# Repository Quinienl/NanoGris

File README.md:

# NanoGrids
### Arduino Nano version of Mutable Instruments Grids

Made this version  with Thru Hole parts and a Arduino Nano.
Schematics are heavely based on Mutable Instruments schematics. This is not a Mutable Instuments product.

_Note: panel hole for button might be a bit to big or small (depends if you use buttoncaps)_

I made this for my own and would like to share it with you. I'm doing this as a hobby so expect support to be like that to ;)
Everything at your own risk..

Some info on my website that might help

https://www.quinie.nl/category/diy/nanogris/

https://www.quinie.nl/nanogris-gallery/

If you don not want to order boards yourself please check out my shop.
https://www.quinie.nl/shop/

hex file for uploading here
https://www.quinie.nl/nanogris-the-hex-file/

Update: 6-8-2021
I updated the name of the module. The current version is 0.041

Older boards will have the same function. Did add some better ground planes. Some silkscreen additions to make build easier and changed the footprint of the potentiometer for better fit.

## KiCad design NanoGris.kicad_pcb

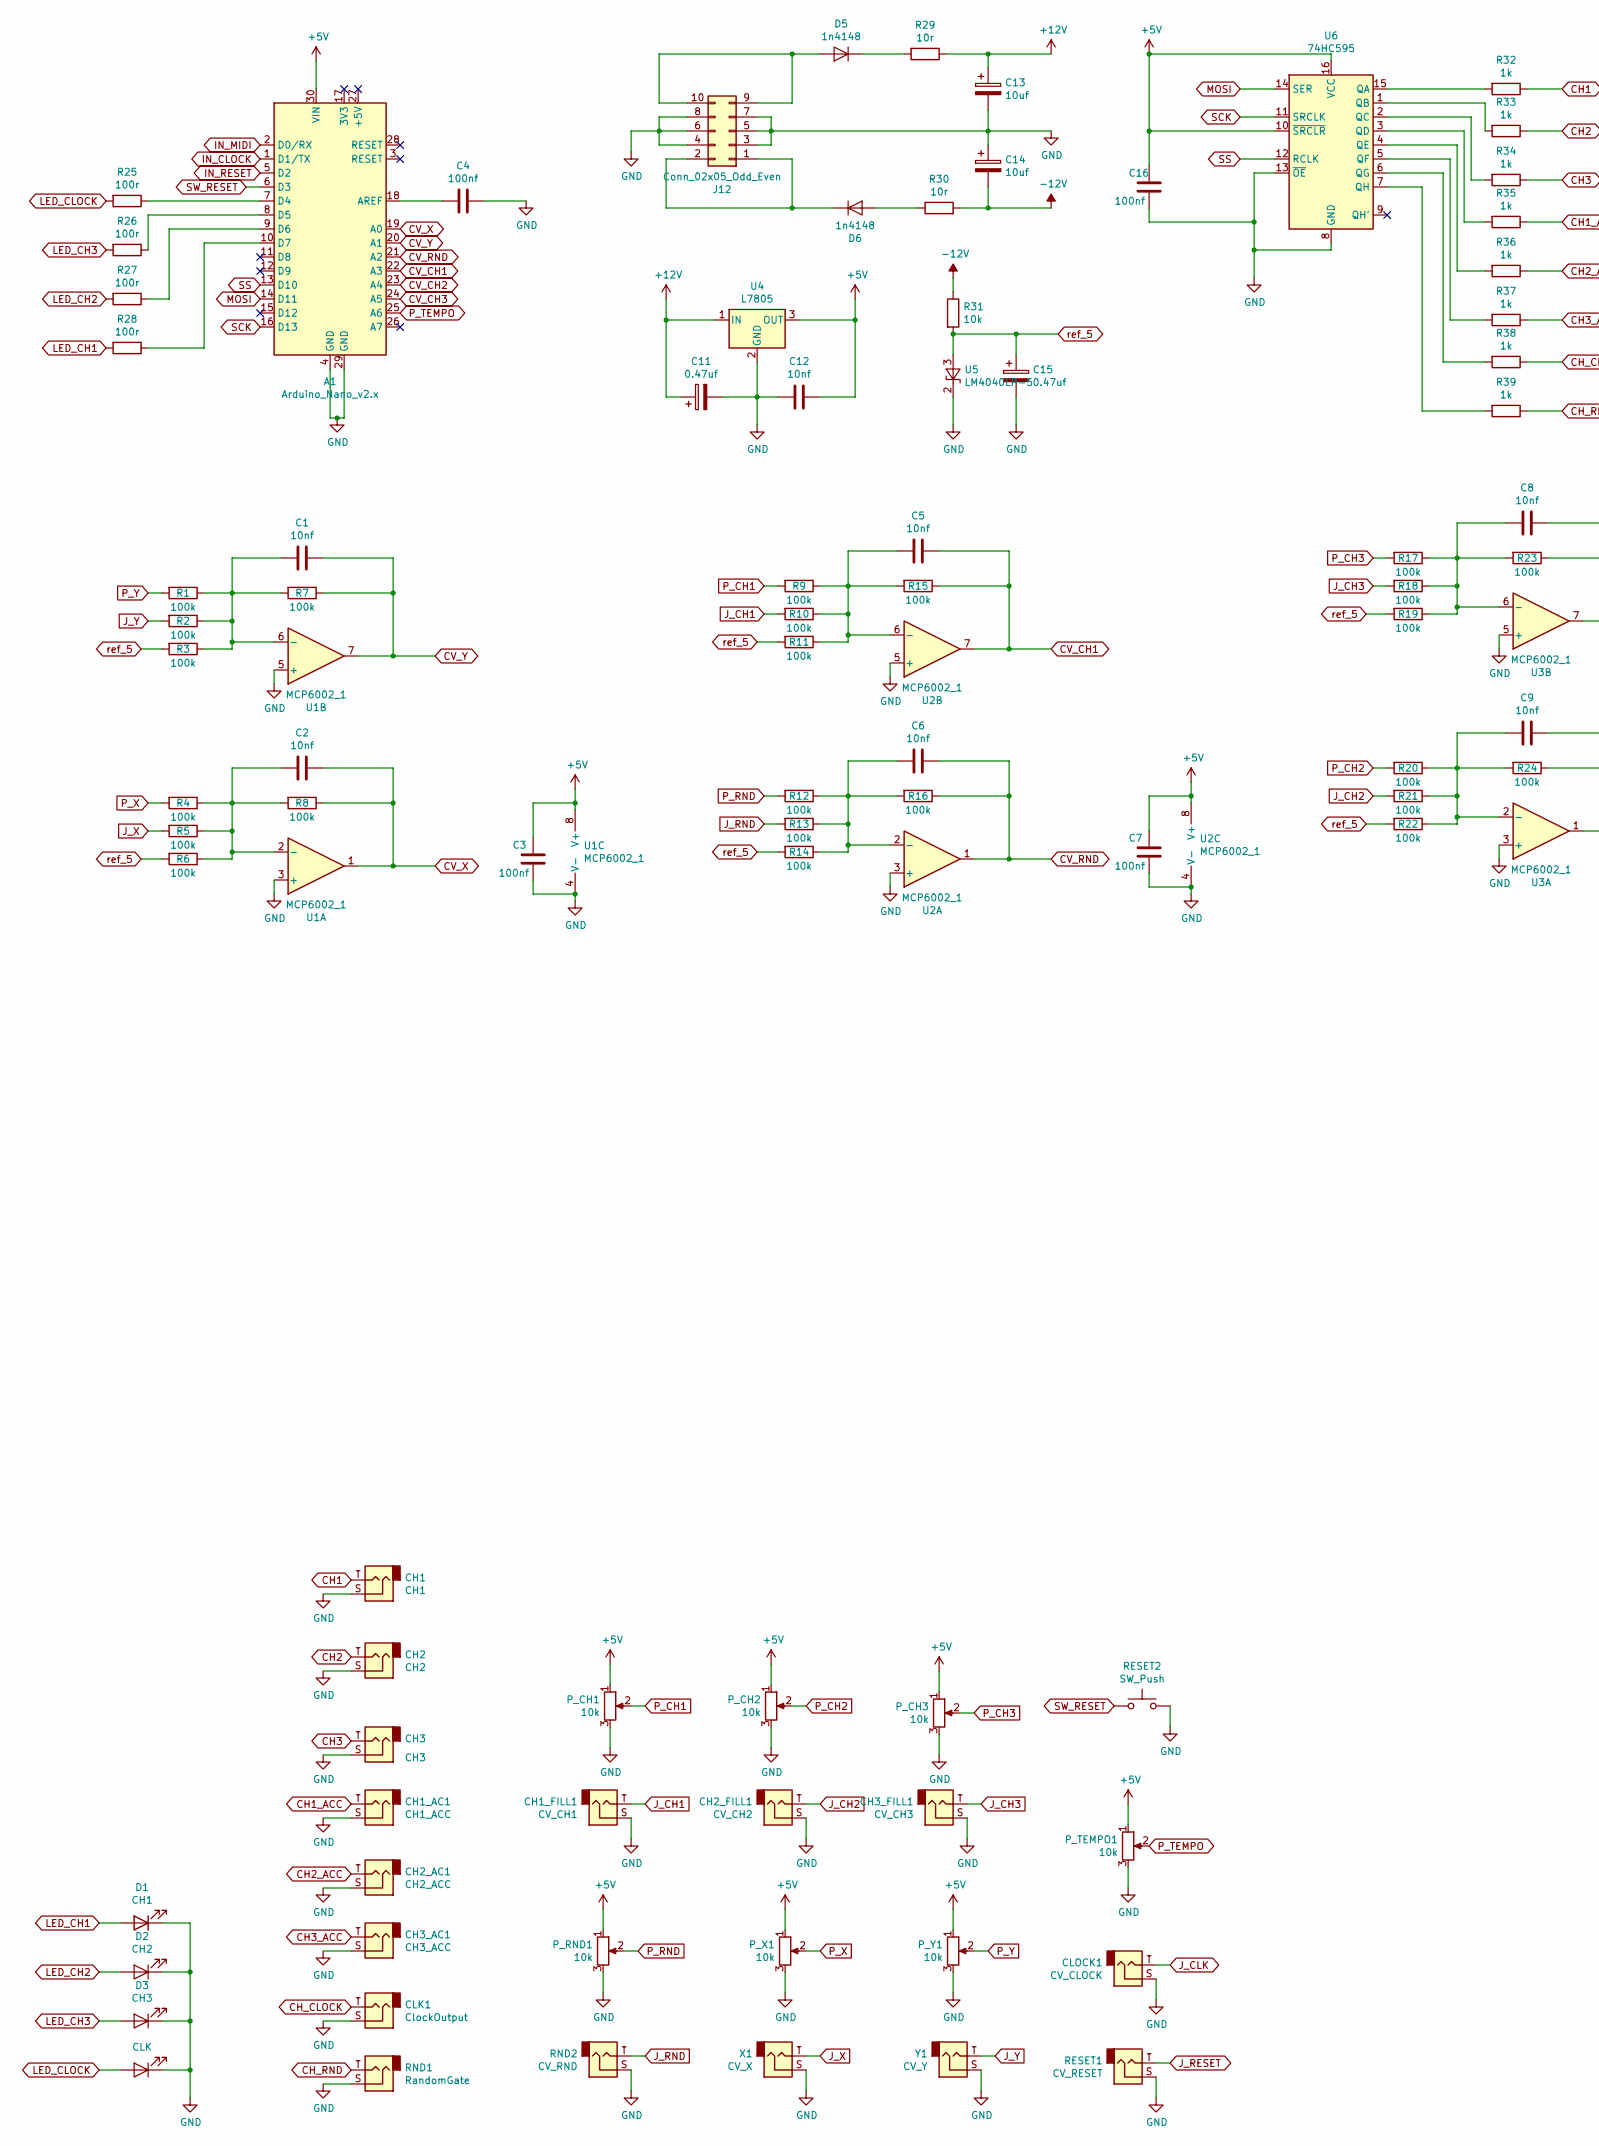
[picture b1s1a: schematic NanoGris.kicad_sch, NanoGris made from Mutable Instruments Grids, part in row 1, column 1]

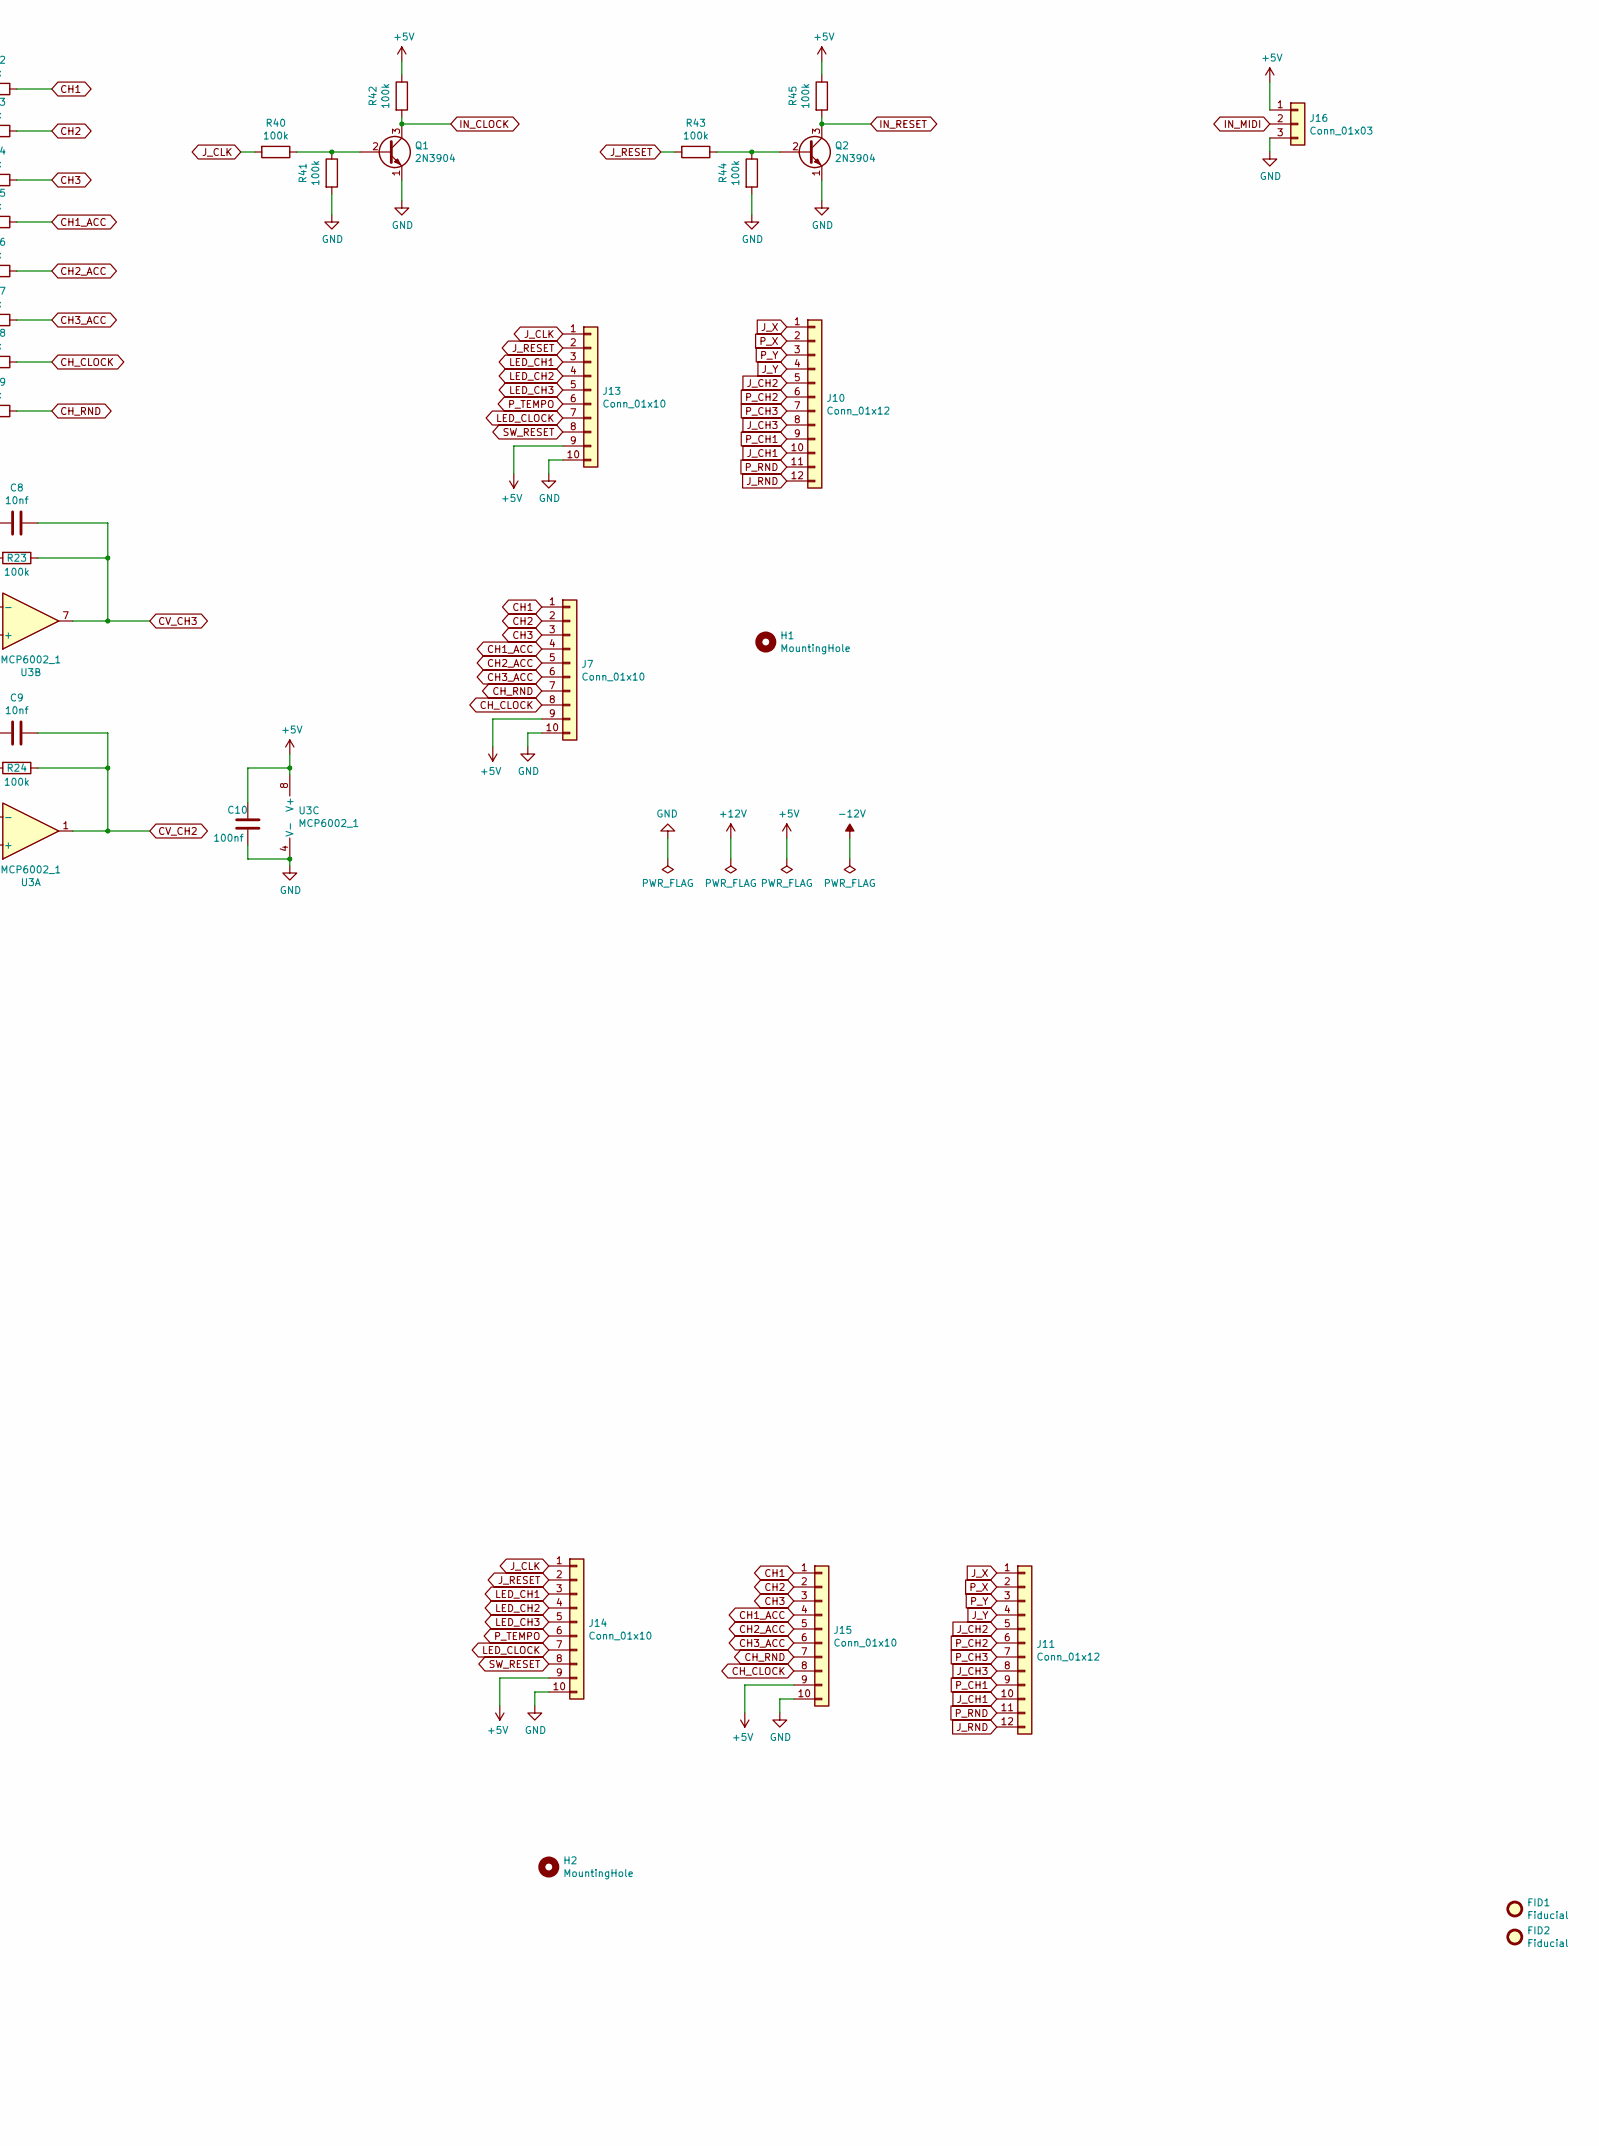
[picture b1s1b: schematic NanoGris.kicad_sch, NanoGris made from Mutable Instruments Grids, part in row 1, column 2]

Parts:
A1: Arduino_Nano_v2.x; Arduino_Nano
C1, C2, C5, C6, C8, C9, C12: 10nf; C_Disc_D5.0mm_W2.5mm_P2.50mm
C3, C4, C7, C10, C16: 100nf; C_Disc_D5.0mm_W2.5mm_P2.50mm
C11, C15: 0.47uf; CP_Radial_D5.0mm_P2.50mm
C13, C14: 10uf; CP_Radial_D5.0mm_P2.50mm
CH1: CH1; Jack_3.5mm_QingPu_WQP-PJ398SM_Vertical_CircularHoles
CH1_AC1: CH1_ACC; Jack_3.5mm_QingPu_WQP-PJ398SM_Vertical_CircularHoles
CH1_FILL1: CV_CH1; Jack_3.5mm_QingPu_WQP-PJ398SM_Vertical_CircularHoles
CH2: CH2; Jack_3.5mm_QingPu_WQP-PJ398SM_Vertical_CircularHoles
CH2_AC1: CH2_ACC; Jack_3.5mm_QingPu_WQP-PJ398SM_Vertical_CircularHoles
CH2_FILL1: CV_CH2; Jack_3.5mm_QingPu_WQP-PJ398SM_Vertical_CircularHoles
CH3: CH3; Jack_3.5mm_QingPu_WQP-PJ398SM_Vertical_CircularHoles
CH3_AC1: CH3_ACC; Jack_3.5mm_QingPu_WQP-PJ398SM_Vertical_CircularHoles
CH3_FILL1: CV_CH3; Jack_3.5mm_QingPu_WQP-PJ398SM_Vertical_CircularHoles
CLK1: ClockOutput; Jack_3.5mm_QingPu_WQP-PJ398SM_Vertical_CircularHoles
CLOCK1: CV_CLOCK; Jack_3.5mm_QingPu_WQP-PJ398SM_Vertical_CircularHoles
D1: CH1; LED_D3.0mm
D2: CH2; LED_D3.0mm
D3: CH3; LED_D3.0mm
D4: CLK; LED_D3.0mm
D5, D6: 1n4148; D_DO-34_SOD68_P7.62mm_Horizontal
FID1: Fiducial; OSHW-Logo2_7.3x6mm_SilkScreen
FID2: Fiducial; OSHW-Logo2_14.6x12mm_SilkScreen
H1, H2: MountingHole; MountingHole_3.2mm_M3
J7, J13: Conn_01x10; PinSocket_1x10_P2.54mm_Vertical
J10: Conn_01x12; PinSocket_1x12_P2.54mm_Vertical
J11: Conn_01x12; PinHeader_1x12_P2.54mm_Vertical
J12: Conn_02x05_Odd_Even; IDC-Header_2x05_P2.54mm_Vertical
J14, J15: Conn_01x10; PinHeader_1x10_P2.54mm_Vertical
J16: Conn_01x03; PinHeader_1x03_P2.54mm_Vertical
P_CH1, P_CH2, P_CH3: 10k; Potentiometer_Alps_RK09K_Single_Vertical_round
P_RND1: 10k; Potentiometer_Alps_RK09K_Single_Vertical_round
P_TEMPO1: 10k; Potentiometer_Alps_RK09K_Single_Vertical_round
P_X1: 10k; Potentiometer_Alps_RK09K_Single_Vertical_round
P_Y1: 10k; Potentiometer_Alps_RK09K_Single_Vertical_round
Q1, Q2: 2N3904; TO-92_Wide
R1, R2, R3, R4, R5, R6, R7, R8, R9, R10, R11, R12, R13, R14, R15, R16, R17, R18, R19, R20, R21, R22, R23, R24, R40, R41, R42, R43, R44, R45: 100k; R_Axial_DIN0204_L3.6mm_D1.6mm_P7.62mm_Horizontal
R25, R26, R27, R28: 100r; R_Axial_DIN0207_L6.3mm_D2.5mm_P7.62mm_Horizontal
R29, R30: 10r; R_Axial_DIN0204_L3.6mm_D1.6mm_P7.62mm_Horizontal
R31: 10k; R_Axial_DIN0204_L3.6mm_D1.6mm_P7.62mm_Horizontal
R32, R33, R34, R35, R36, R37, R38, R39: 1k; R_Axial_DIN0204_L3.6mm_D1.6mm_P7.62mm_Horizontal
RESET1: CV_RESET; Jack_3.5mm_QingPu_WQP-PJ398SM_Vertical_CircularHoles
RESET2: SW_Push; SW_PUSH_6mm
RND1: RandomGate; Jack_3.5mm_QingPu_WQP-PJ398SM_Vertical_CircularHoles
RND2: CV_RND; Jack_3.5mm_QingPu_WQP-PJ398SM_Vertical_CircularHoles
U1, U2, U3: MCP6002_1; DIP-8_W7.62mm
U4: L7805; TO-220-3_Vertical
U5: LM4040LP-5; TO-92_Wide
U6: 74HC595; DIP-16_W7.62mm
X1: CV_X; Jack_3.5mm_QingPu_WQP-PJ398SM_Vertical_CircularHoles
Y1: CV_Y; Jack_3.5mm_QingPu_WQP-PJ398SM_Vertical_CircularHoles

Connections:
+5V: A1.30 (VIN), C3.1, C7.1, C10.1, C12.1, C16.1, J7.9, J13.9, J14.9, J15.9, J16.1, P_CH1.1, P_CH2.1, P_CH3.1, P_RND1.1, P_TEMPO1.1, P_X1.1, P_Y1.1, R42.1, R45.1, U1.8 (V+), U2.8 (V+), U3.8 (V+), U4.3 (OUT), U6.10 (~SRCLR), U6.16 (VCC)
+12V: C11.1, C13.1, R29.1, U4.1 (IN)
-12V: C14.2, R30.2, R31.1
CH1: CH1.T, J7.1, J15.1, R32.1
CH1_ACC: CH1_AC1.T, J7.4, J15.4, R35.1
CH2: CH2.T, J7.2, J15.2, R33.1
CH2_ACC: CH2_AC1.T, J7.5, J15.5, R36.1
CH3: CH3.T, J7.3, J15.3, R34.1
CH3_ACC: CH3_AC1.T, J7.6, J15.6, R37.1
CH_CLOCK: CLK1.T, J7.8, J15.8, R38.1
CH_RND: J7.7, J15.7, R39.1, RND1.T
CV_CH1: A1.22 (A3), C5.1, R15.1, U2.7
CV_CH2: A1.23 (A4), C9.1, R24.1, U3.1
CV_CH3: A1.24 (A5), C8.1, R23.1, U3.7
CV_RND: A1.21 (A2), C6.1, R16.1, U2.1
CV_X: A1.19 (A0), C2.1, R8.1, U1.1
CV_Y: A1.20 (A1), C1.1, R7.1, U1.7
GND: A1.4 (GND), A1.29 (GND), C3.2, C4.1, C7.2, C10.2, C11.2, C12.2, C13.2, C14.1, C15.2, C16.2, CH1.S, CH1_AC1.S, CH1_FILL1.S, CH2.S, CH2_AC1.S, CH2_FILL1.S, CH3.S, CH3_AC1.S, CH3_FILL1.S, CLK1.S, CLOCK1.S, D1.1 (K), D2.1 (K), D3.1 (K), D4.1 (K), J7.10, J12.3, J12.4, J12.5, J12.6, J12.7, J12.8, J13.10, J14.10, J15.10, J16.3, P_CH1.3, P_CH2.3, P_CH3.3, P_RND1.3, P_TEMPO1.3, P_X1.3, P_Y1.3, Q1.1 (E), Q2.1 (E), R41.2, R44.2, RESET1.S, RESET2.2, RND1.S, RND2.S, U1.3 (+), U1.4 (V-), U1.5 (+), U2.3 (+), U2.4 (V-), U2.5 (+), U3.3 (+), U3.4 (V-), U3.5 (+), U4.2 (GND), U5.2 (K), U6.8 (GND), U6.13 (~OE), X1.S, Y1.S
IN_CLOCK: A1.1 (D1/TX), Q1.3 (C), R42.2
IN_MIDI: A1.2 (D0/RX), J16.2
IN_RESET: A1.5 (D2), Q2.3 (C), R45.2
J_CH1: CH1_FILL1.T, J10.10, J11.10, R10.2
J_CH2: CH2_FILL1.T, J10.5, J11.5, R21.2
J_CH3: CH3_FILL1.T, J10.8, J11.8, R18.2
J_CLK: CLOCK1.T, J13.1, J14.1, R40.2
J_RESET: J13.2, J14.2, R43.2, RESET1.T
J_RND: J10.12, J11.12, R13.2, RND2.T
J_X: J10.1, J11.1, R5.2, X1.T
J_Y: J10.4, J11.4, R2.2, Y1.T
LED_CH1: D1.2 (A), J13.3, J14.3, R28.2
LED_CH2: D2.2 (A), J13.4, J14.4, R27.2
LED_CH3: D3.2 (A), J13.5, J14.5, R26.2
LED_CLOCK: D4.2 (A), J13.7, J14.7, R25.2
MOSI: A1.14 (D11), U6.14 (SER)
unnamed: A1.7 (D4), R25.1
unnamed: A1.8 (D5), R26.1
unnamed: A1.9 (D6), R27.1
unnamed: A1.10 (D7), R28.1
unnamed: A1.18 (AREF), C4.2
unnamed: C1.2, R1.1, R2.1, R3.1, R7.2, U1.6 (-)
unnamed: C2.2, R4.1, R5.1, R6.1, R8.2, U1.2 (-)
unnamed: C5.2, R9.1, R10.1, R11.1, R15.2, U2.6 (-)
unnamed: C6.2, R12.1, R13.1, R14.1, R16.2, U2.2 (-)
unnamed: C8.2, R17.1, R18.1, R19.1, R23.2, U3.6 (-)
unnamed: C9.2, R20.1, R21.1, R22.1, R24.2, U3.2 (-)
unnamed: D5.1 (K), R29.2
unnamed: D5.2 (A), J12.9, J12.10
unnamed: D6.1 (K), J12.1, J12.2
unnamed: D6.2 (A), R30.1
unnamed: Q1.2 (B), R40.1, R41.1
unnamed: Q2.2 (B), R43.1, R44.1
unnamed: R32.2, U6.15 (QA)
unnamed: R33.2, U6.1 (QB)
unnamed: R34.2, U6.2 (QC)
unnamed: R35.2, U6.3 (QD)
unnamed: R36.2, U6.4 (QE)
unnamed: R37.2, U6.5 (QF)
unnamed: R38.2, U6.6 (QG)
unnamed: R39.2, U6.7 (QH)
P_CH1: J10.9, J11.9, P_CH1.2, R9.2
P_CH2: J10.6, J11.6, P_CH2.2, R20.2
P_CH3: J10.7, J11.7, P_CH3.2, R17.2
P_RND: J10.11, J11.11, P_RND1.2, R12.2
P_TEMPO: A1.25 (A6), J13.6, J14.6, P_TEMPO1.2
P_X: J10.2, J11.2, P_X1.2, R4.2
P_Y: J10.3, J11.3, P_Y1.2, R1.2
SCK: A1.16 (D13), U6.11 (SRCLK)
SS: A1.13 (D10), U6.12 (RCLK)
SW_RESET: A1.6 (D3), J13.8, J14.8, RESET2.1
ref_5: C15.1, R3.2, R6.2, R11.2, R14.2, R19.2, R22.2, R31.2, U5.3 (A)

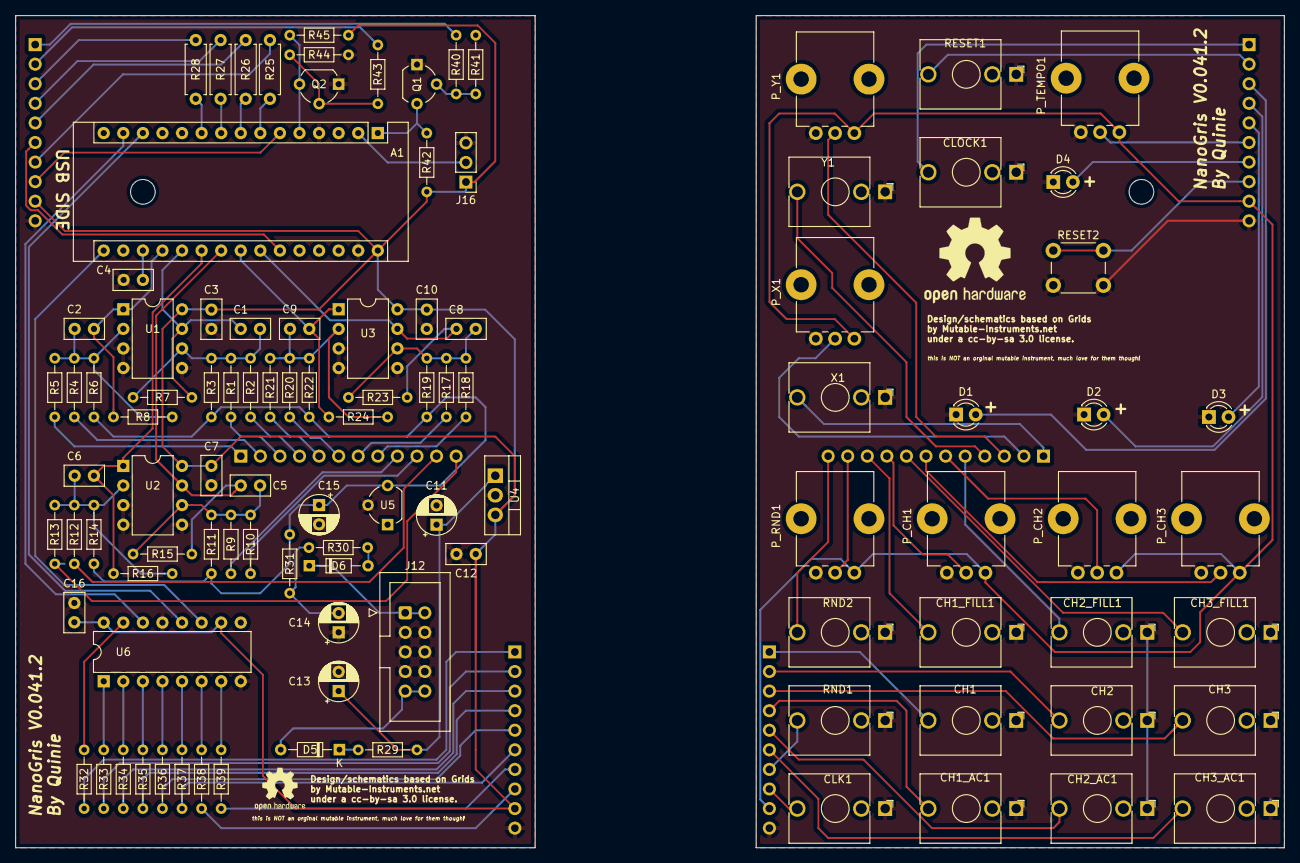
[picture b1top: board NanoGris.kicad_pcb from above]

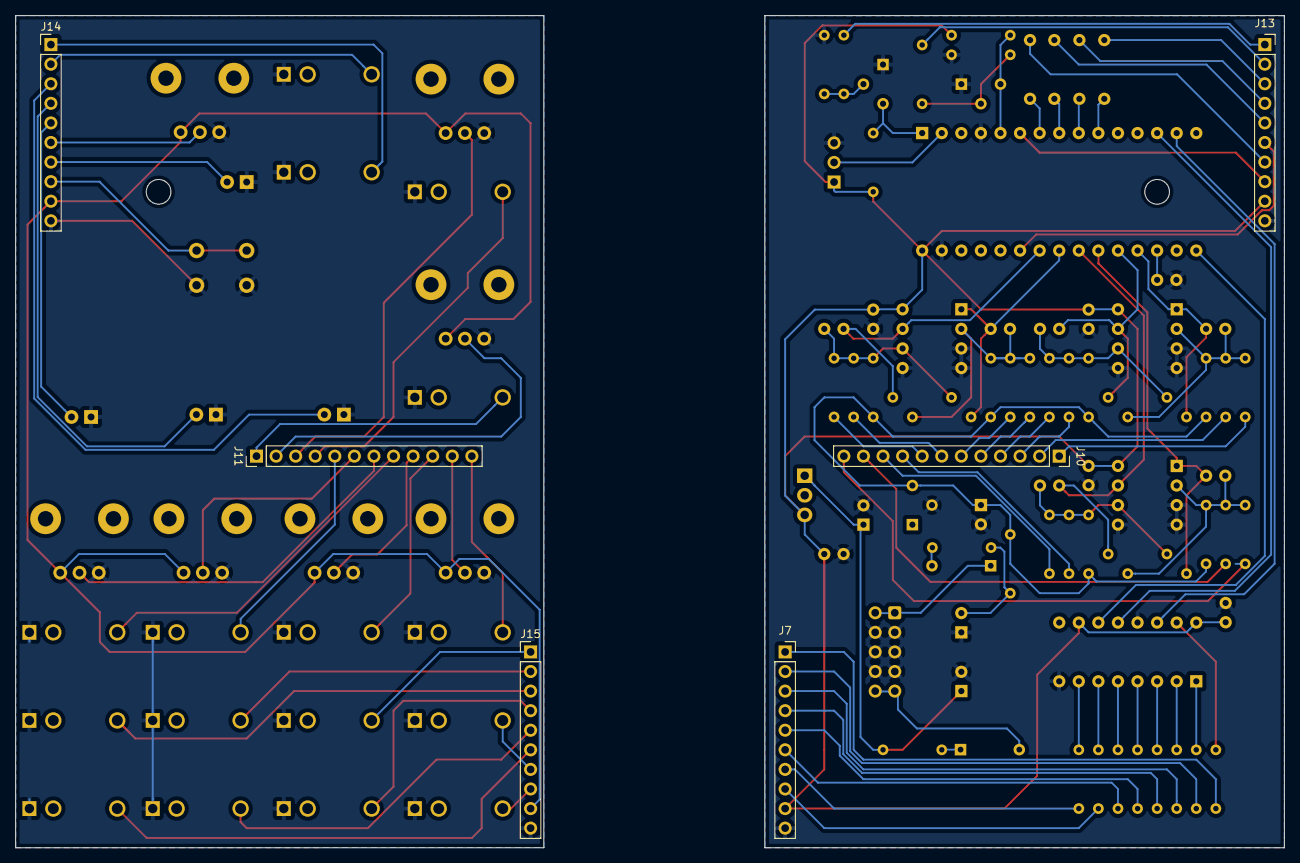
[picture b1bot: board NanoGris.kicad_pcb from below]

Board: 2 copper layers, 164.6 x 108.0 mm, 112 parts (6 on the bottom side), 70 nets.

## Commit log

2020-03-28 Images
    Added images
2020-03-28 change size of image
2021-06-26 Updates 0.04
    Updates for 0.04
    Change footprint for pots
    Added + sign for leds
    Added usb side
    Added Ground plane
2021-06-26 bak files
    Removed
2021-06-26 Panel
    Bigger holes for pots
2021-06-26 0.04 Commit
    Gerbers
2021-06-27 Panel Gerbers
    Panel Gerbers 0.04
2021-07-28 Panel update + IBOM
    missing mounting holes fixed
    Ibom added
2021-07-28 Gerbers and small update
    Panel Gerber and fixed some holes
2021-07-28 Gerbers
2021-07-28 Circular panel gerbers
2021-07-29 Gerber Update
2021-08-06 Rename
2021-08-23 Ibom name update
2022-05-20 Bom Update (R31 needs to be 10K)
    Error inBOM R31 needs to be 10k
    https://www.quinie.nl/nanogris-big-bom-mistake-update-for-better-range-on-pots/
2022-10-15 Updated powerheader
    Now with correct power schematic and boxed header.

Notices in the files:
NanoGris.kicad_pcb:
under a cc-by-sa 3.0 license.
